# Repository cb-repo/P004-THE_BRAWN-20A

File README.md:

# THE BRAWN - 20A (v1.0)

THE BRAWN is a single DC-motor ESC: originally designed for insect-weight combat-robots, but is suitable for any appliction requiring a lightweight motor driver. 

Designed and built in [Christchurch, New Zealand ](https://www.google.co.nz/maps/place/Christchurch+New+Zealand) by Connor Benton, visit [cb-technology](https://www.cb-technology.co.nz/) for details.

## FEATURES
- Single Bi-Directional DC-motor output.
- Ultra-compact and lightweight.
- Under-voltage and reverse-polarity battery input protections.
- Run and status LED's.
- Instant power on and brown out recovery.
- Internal BEC for recievers.
- Includes a 100nF capacitor across the motor output to filter noise and voltage spikes.

## SPECIFICATIONS
- **Dimensions:** 20x15x4 mm
- **Weight:** 1.7g *excluding wires*
- **Input Voltage - Rated:** 1-3S lipo (3.3-12.6V)
- **Input Voltage - Absolute Max:** 18V
- **Output Current - Continuious:** 10A *(for more infomation see the Current Rating seciton)*
- **Output Current - Pulse:** 66A 
- **Motor Braking:** Enabled
- **BEC:** 3.3V, 200mA. Designed to power the radio reciever and other downstream ESC's but no motors or servos.
- **Signal Input:** Standard Servo PWM
     
## Fault Conditions
 - **Under-Voltage:** An under-voltage event occurs when the battery voltage falls below a pre-determined threshold.
    - At 3.6V (per cell) the device enters a warning state. This is only a warning and so functionality is not affected but the warning LED is illuminated for the operator.
    - At 3.4V (per cell) the device enters an under-voltage fault state. All motor functionality will be stopped until battery voltage is restored.
 - **Signal-Input:** A signal-input fault will occur if connection to the radio is lost for 50 ms. 
    - During a signal-input fault, a 'No Signal' fail-safe method is implemented and THE BRAWN will stop driving the motor output.
    - When a radio connection has been re-established the motor functionality is immediately resumed.

## LED Behaviour
There are two LEDs on THE BRAWN: 1x red Run LED and 1x green Status LED. The behaviour of each LED indicates what state the device is in.
 - **Normal Operation** Red: ON, Green: OFF
 - **Warning: Low Battery** Red: ON, Green: Flash
 - **Fault: Under-Voltage:** Red: Flash, Green: Flash
 - **Fault: Signal Input:** Red: OFF, Green: Flash

## Current Rating
The current rating of THE BRAWN is temperature-limited and so is very dependednt on the wires (gauge, length, and insulation) and avalible cooling. It is the responsibility of the user to choose the correct wires and test it appropriately before stressing the THE BRAWN in combat. 

As a guide, constant-current thermal testing has been conducted to illistrate the thermal characteristics. *Note: This test has been conducted at constant current, resulting in a higher temperature than the pulse currents in many drive applications.*

##### Reference testing parameters:
 - **Voltage:** 12V
 - **Motor Wire Length:** 100 mm
 - **Battery Wire Length:** 100 mm
 - **Wire Insulation:** PVC
 - **Ambient Temperature:** 23.5 °C
 - **PCB Heatshrink:** Yes
 - **ESC Cooling:** Open-Air passive cooling

##### Constant Current = 5A

##### Constant Current = 8A

##### Constant Current = 10A

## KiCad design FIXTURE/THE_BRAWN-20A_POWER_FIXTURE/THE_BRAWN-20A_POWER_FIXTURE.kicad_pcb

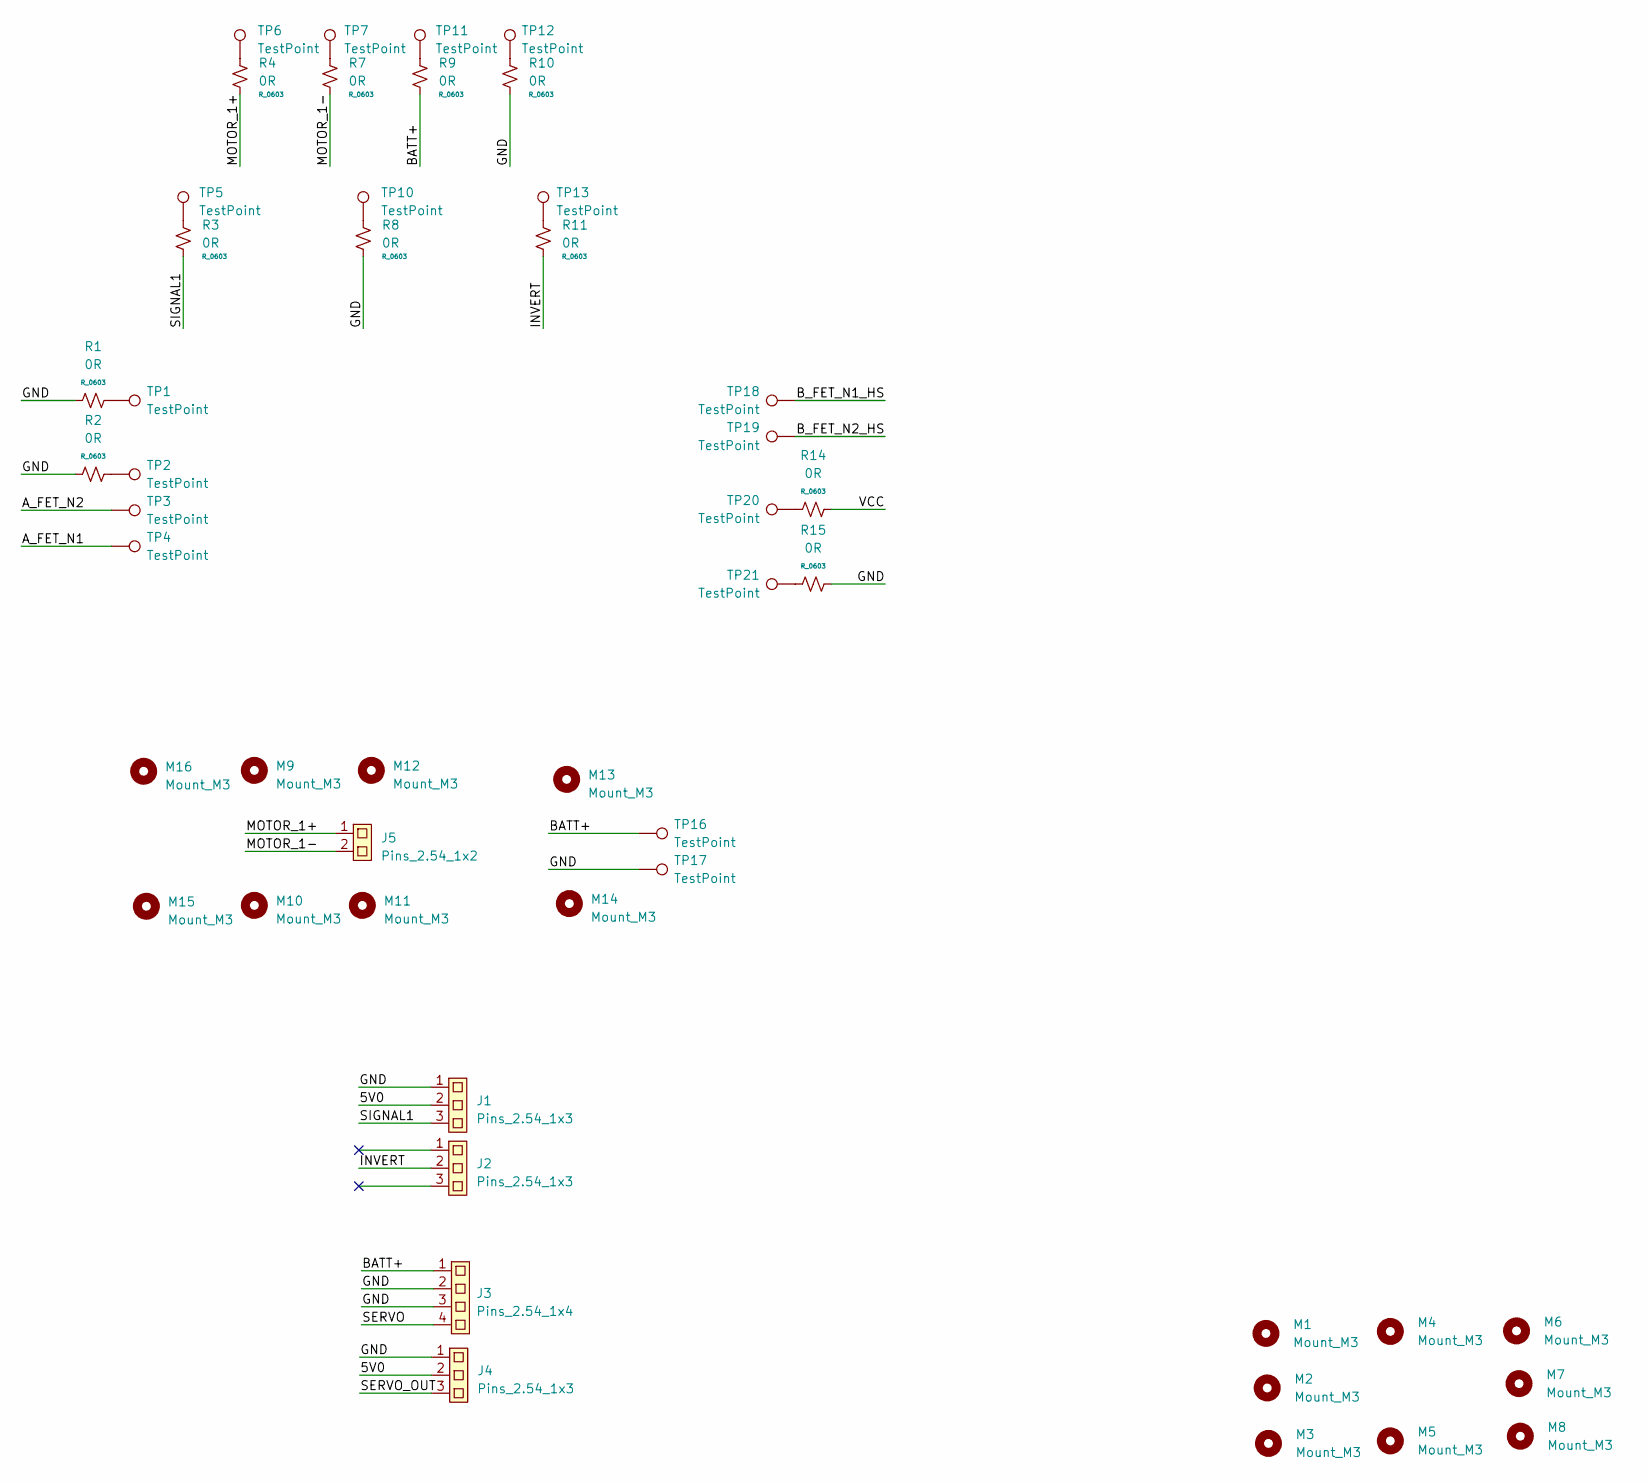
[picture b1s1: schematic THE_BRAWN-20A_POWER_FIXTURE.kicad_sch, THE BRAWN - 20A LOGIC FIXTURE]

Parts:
J1, J2, J4: Pins_2.54_1x3; Pins-2.54-1x3
J3: Pins_2.54_1x4; Pins-2.54-1x4
J5: Pins_2.54_1x2; Pins-2.54-1x2
M1, M2, M3, M4, M5, M6, M7, M8, M9, M10, M11, M12, M13, M14, M15, M16: Mount_M3
R1, R2, R3, R4, R7, R8, R9, R10, R11, R14, R15: 0R; R_0603
TP1, TP2, TP3, TP4, TP5, TP6, TP7, TP10, TP11, TP12, TP13, TP16, TP17, TP18, TP19, TP20, TP21: TestPoint; TestPoint_THTPad_D3.0mm_Drill1.5mm

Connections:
/5V0: J1.2, J4.2
/A_FET_N1: TP4.1
/A_FET_N2: TP3.1
/BATT+: J3.1, R9.2, TP16.1
/B_FET_N1_HS: TP18.1
/B_FET_N2_HS: TP19.1
/GND: J1.1, J3.2, J3.3, J4.1, R1.1, R2.1, R8.2, R10.2, R15.2, TP17.1
/INVERT: J2.2, R11.2
/MOTOR_1+: J5.1, R4.2
/MOTOR_1-: J5.2, R7.2
/SERVO: J3.4
/SERVO_OUT: J4.3
/SIGNAL1: J1.3, R3.2
/VCC: R14.2
unnamed: R1.2, TP1.1
unnamed: R2.2, TP2.1
unnamed: R3.1, TP5.1
unnamed: R4.1, TP6.1
unnamed: R7.1, TP7.1
unnamed: R8.1, TP10.1
unnamed: R9.1, TP11.1
unnamed: R10.1, TP12.1
unnamed: R11.1, TP13.1
unnamed: R14.1, TP20.1
unnamed: R15.1, TP21.1

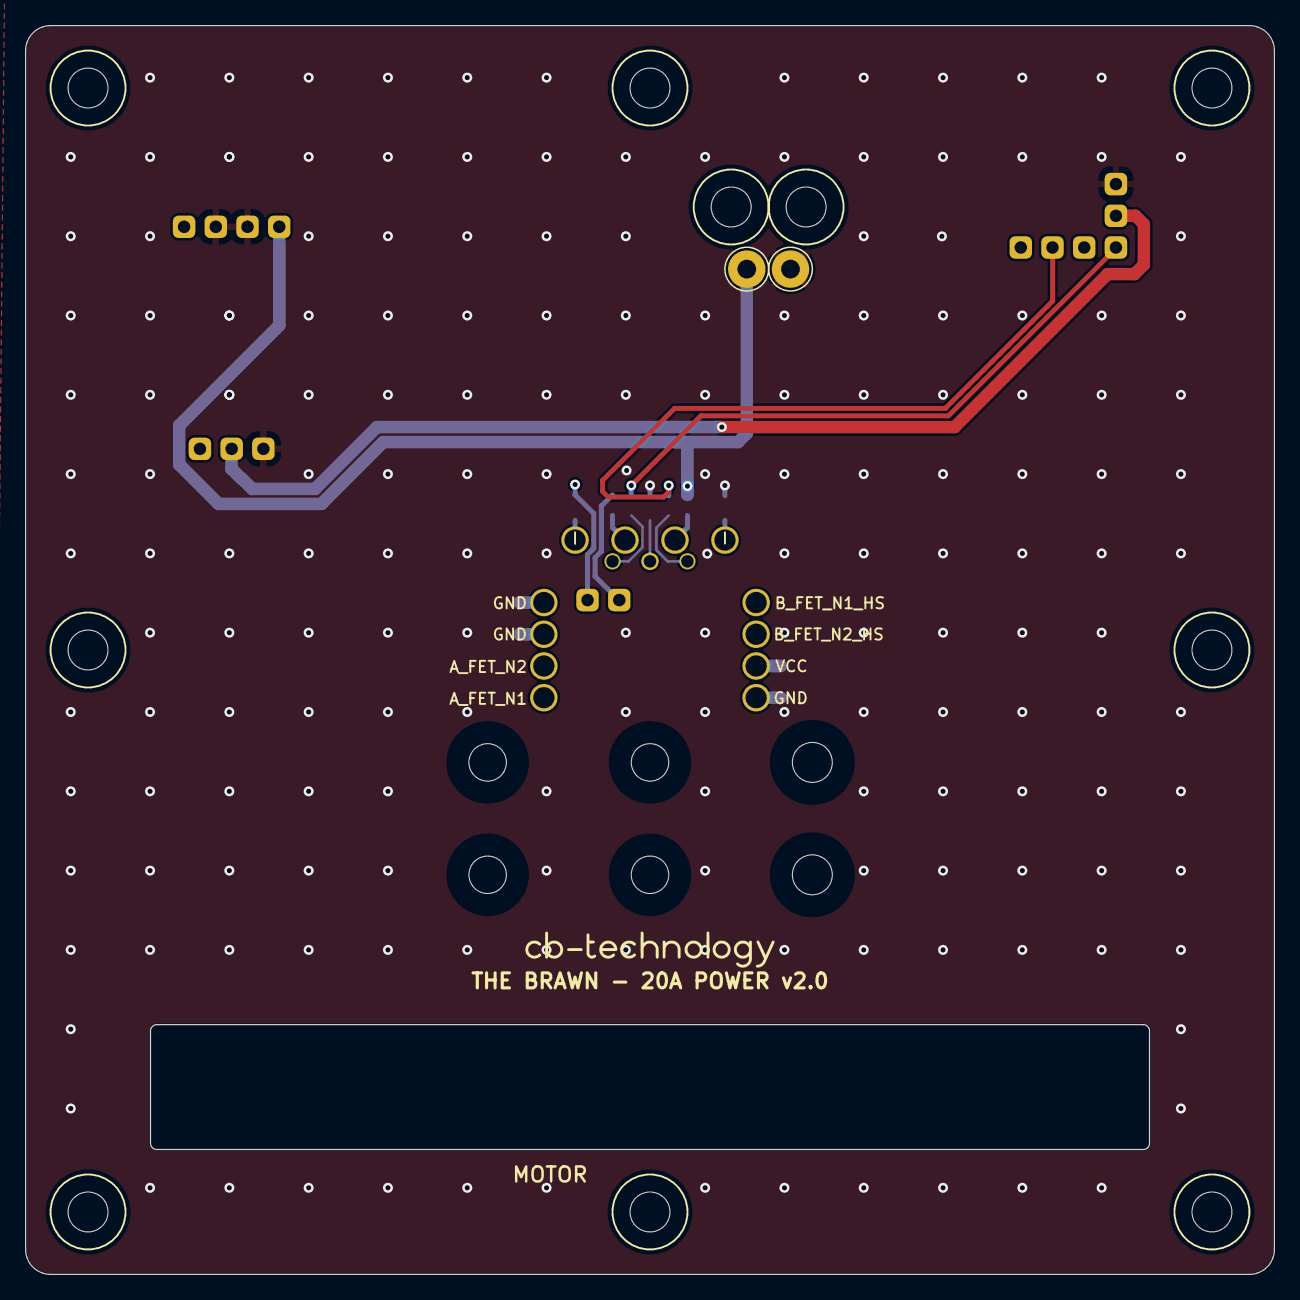
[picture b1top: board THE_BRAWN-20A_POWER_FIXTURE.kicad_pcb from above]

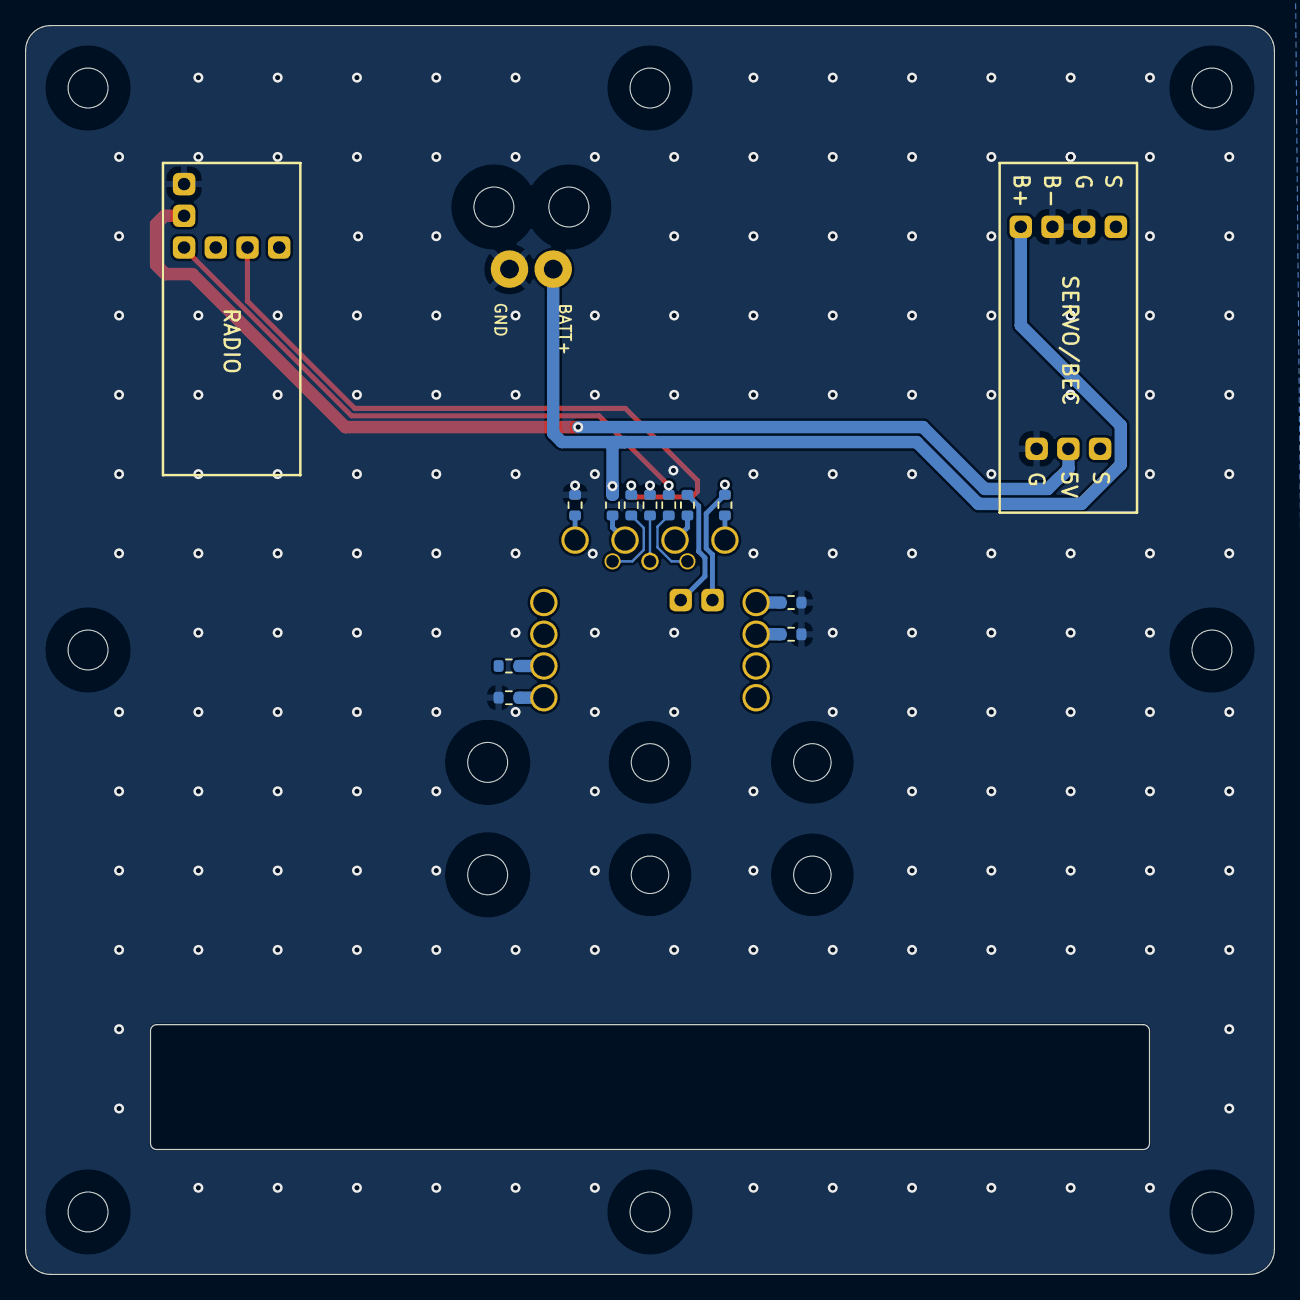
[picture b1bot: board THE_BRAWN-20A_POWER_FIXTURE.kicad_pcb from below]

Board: 2 copper layers, 100.0 x 100.0 mm, 49 parts (19 on the bottom side), 18 nets.

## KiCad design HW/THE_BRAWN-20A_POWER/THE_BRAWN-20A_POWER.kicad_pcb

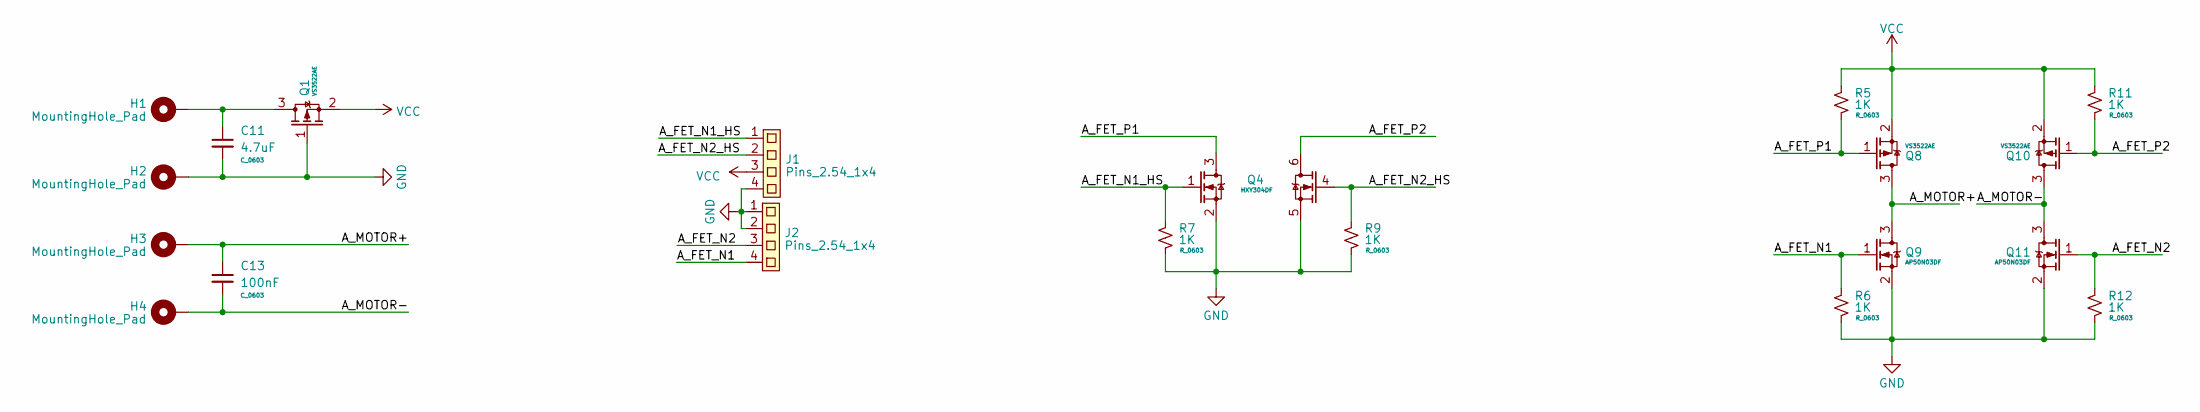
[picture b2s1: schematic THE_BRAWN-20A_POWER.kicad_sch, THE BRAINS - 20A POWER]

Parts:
C11: 4.7uF; C_0603
C13: 100nF; C_0603
H1, H2, H3, H4: MountingHole_Pad; MountingHole_2.2mm_M2_Pad_TopBottom
J1, J2: Pins_2.54_1x4; Pins-2.54-1x4
Q1, Q8, Q10: VS3522AE; 8-DFN_3x3
Q4: HXY304DF; 8-DFN_3x3_DUAL
Q9, Q11: AP50N03DF; 8-DFN_3x3
R5, R6, R7, R9, R11, R12: 1K; R_0603

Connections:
/A_FET_N1: J2.4, Q9.1 (G), R6.1
/A_FET_N1_HS: J1.1, Q4.1 (G), R7.1
/A_FET_N2: J2.3, Q11.1 (G), R12.1
/A_FET_N2_HS: J1.2, Q4.4 (G), R9.1
/A_FET_P1: Q4.3 (D), Q8.1 (G), R5.2
/A_FET_P2: Q4.6 (D), Q10.1 (G), R11.2
/A_MOTOR+: C13.1, H3.1, Q8.3 (D), Q9.3 (D)
/A_MOTOR-: C13.2, H4.1, Q10.3 (D), Q11.3 (D)
GND: C11.2, H2.1, J1.4, J2.1, J2.2, Q1.1 (G), Q4.2 (S), Q4.5 (S), Q9.2 (S), Q11.2 (S), R6.2, R7.2, R9.2, R12.2
unnamed: C11.1, H1.1, Q1.3 (D)
VCC: J1.3, Q1.2 (S), Q8.2 (S), Q10.2 (S), R5.1, R11.1

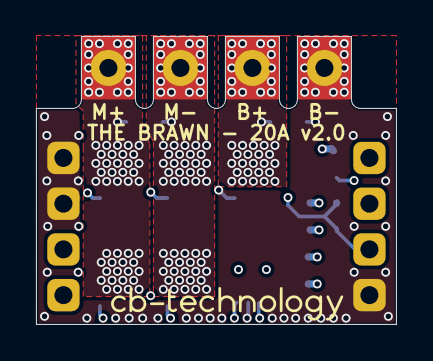
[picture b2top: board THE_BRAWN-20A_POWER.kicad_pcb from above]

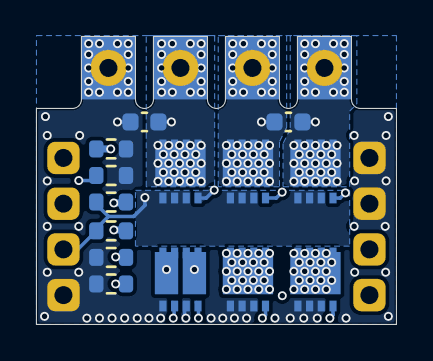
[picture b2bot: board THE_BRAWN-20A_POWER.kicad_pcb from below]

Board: 4 copper layers, 20.0 x 16.0 mm, 20 parts (14 on the bottom side), 11 nets.

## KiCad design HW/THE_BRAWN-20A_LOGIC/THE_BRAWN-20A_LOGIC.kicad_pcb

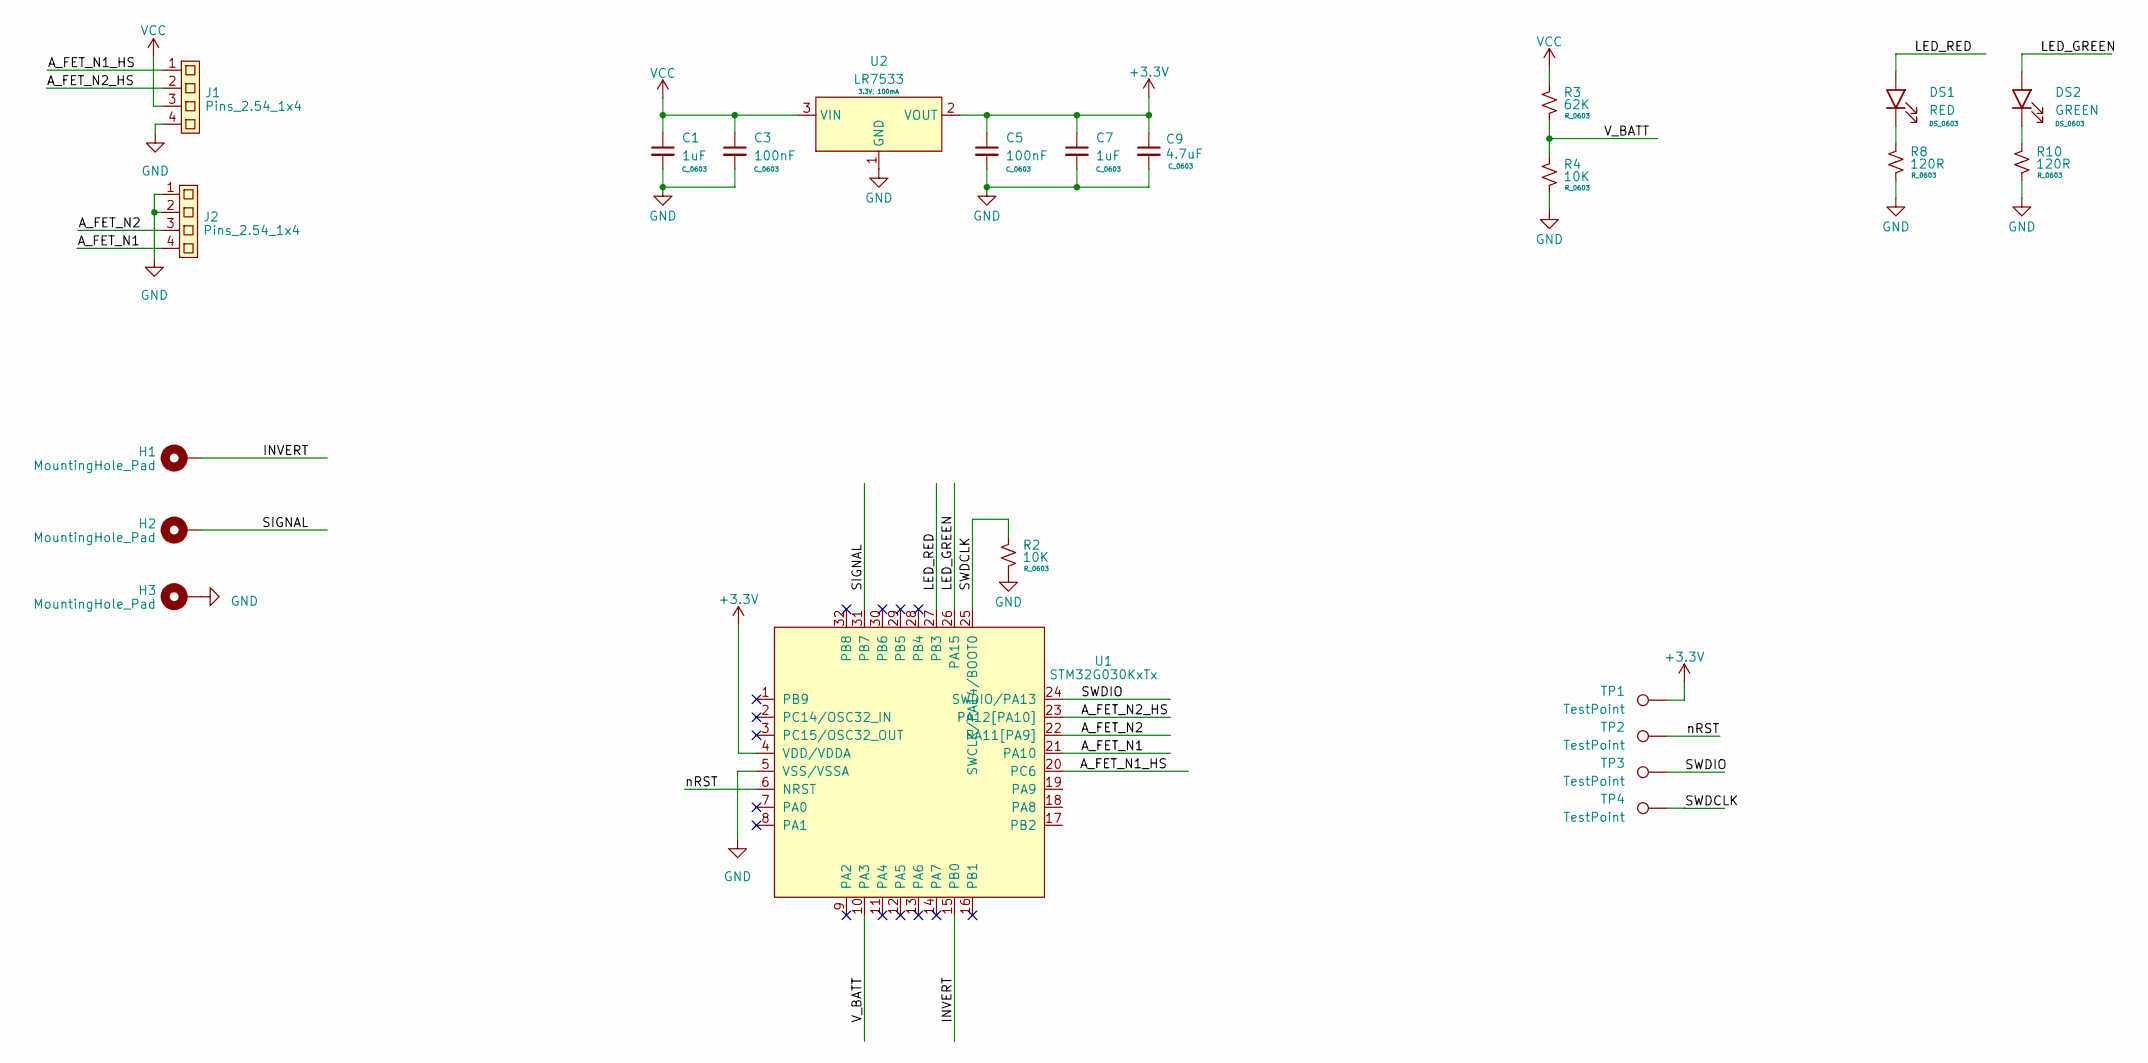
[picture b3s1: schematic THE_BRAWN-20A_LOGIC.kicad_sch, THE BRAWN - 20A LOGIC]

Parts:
C1, C7: 1uF; C_0603
C3, C5: 100nF; C_0603
C9: 4.7uF; C_0603
DS1: RED; DS_0603
DS2: GREEN; DS_0603
H1, H2, H3: MountingHole_Pad; MountingHole_2.2mm_M2_Pad_TopBottom
J1, J2: Pins_2.54_1x4; Pins-2.54-1x4
R2, R4: 10K; R_0603
R3: 62K; R_0603
R8, R10: 120R; R_0603
TP1, TP2, TP3, TP4: TestPoint; TestPoint_Pad_D1.5mm
U1: STM32G030KxTx; LQFP32_08_7x7
U2: LR7533; SOT23_3

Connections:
+3.3V: C5.1, C7.1, C9.1, TP1.1, U1.4 (VDD/VDDA), U2.2 (VOUT)
/A_FET_N1: J2.4, U1.21 (PA10)
/A_FET_N1_HS: J1.1, U1.20 (PC6)
/A_FET_N2: J2.3, U1.22 (PA11[PA9])
/A_FET_N2_HS: J1.2, U1.23 (PA12[PA10])
/INVERT: H1.1, U1.15 (PB0)
/LED_GREEN: DS2.2 (A), U1.26 (PA15)
/LED_RED: DS1.2 (A), U1.27 (PB3)
/SIGNAL: H2.1, U1.31 (PB7)
/SWDCLK: R2.1, TP4.1, U1.25 (SWCLK/PA14/BOOT0)
/SWDIO: TP3.1, U1.24 (SWDIO/PA13)
/V_BATT: R3.2, R4.1, U1.10 (PA3)
/nRST: TP2.1, U1.6 (NRST)
GND: C1.2, C3.2, C5.2, C7.2, C9.2, H3.1, J1.4, J2.1, J2.2, R2.2, R4.2, R8.2, R10.2, U1.5 (VSS/VSSA), U2.1 (GND)
unnamed: DS1.1 (K), R8.1
unnamed: DS2.1 (K), R10.1
VCC: C1.1, C3.1, J1.3, R3.1, U2.3 (VIN)

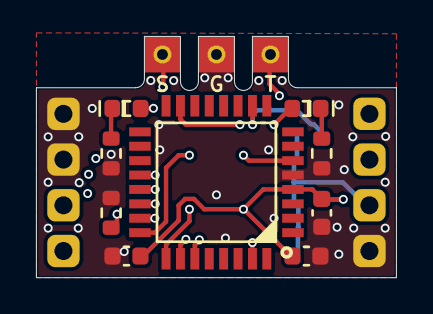
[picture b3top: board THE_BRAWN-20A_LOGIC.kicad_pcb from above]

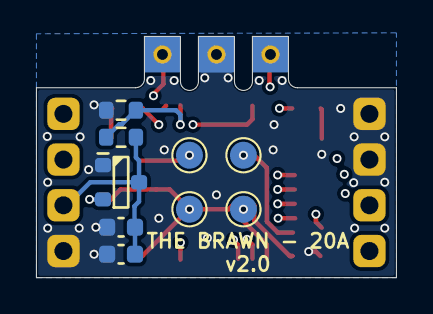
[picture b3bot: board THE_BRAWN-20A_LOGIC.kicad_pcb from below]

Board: 4 copper layers, 20.0 x 13.4 mm, 23 parts (9 on the bottom side), 17 nets.

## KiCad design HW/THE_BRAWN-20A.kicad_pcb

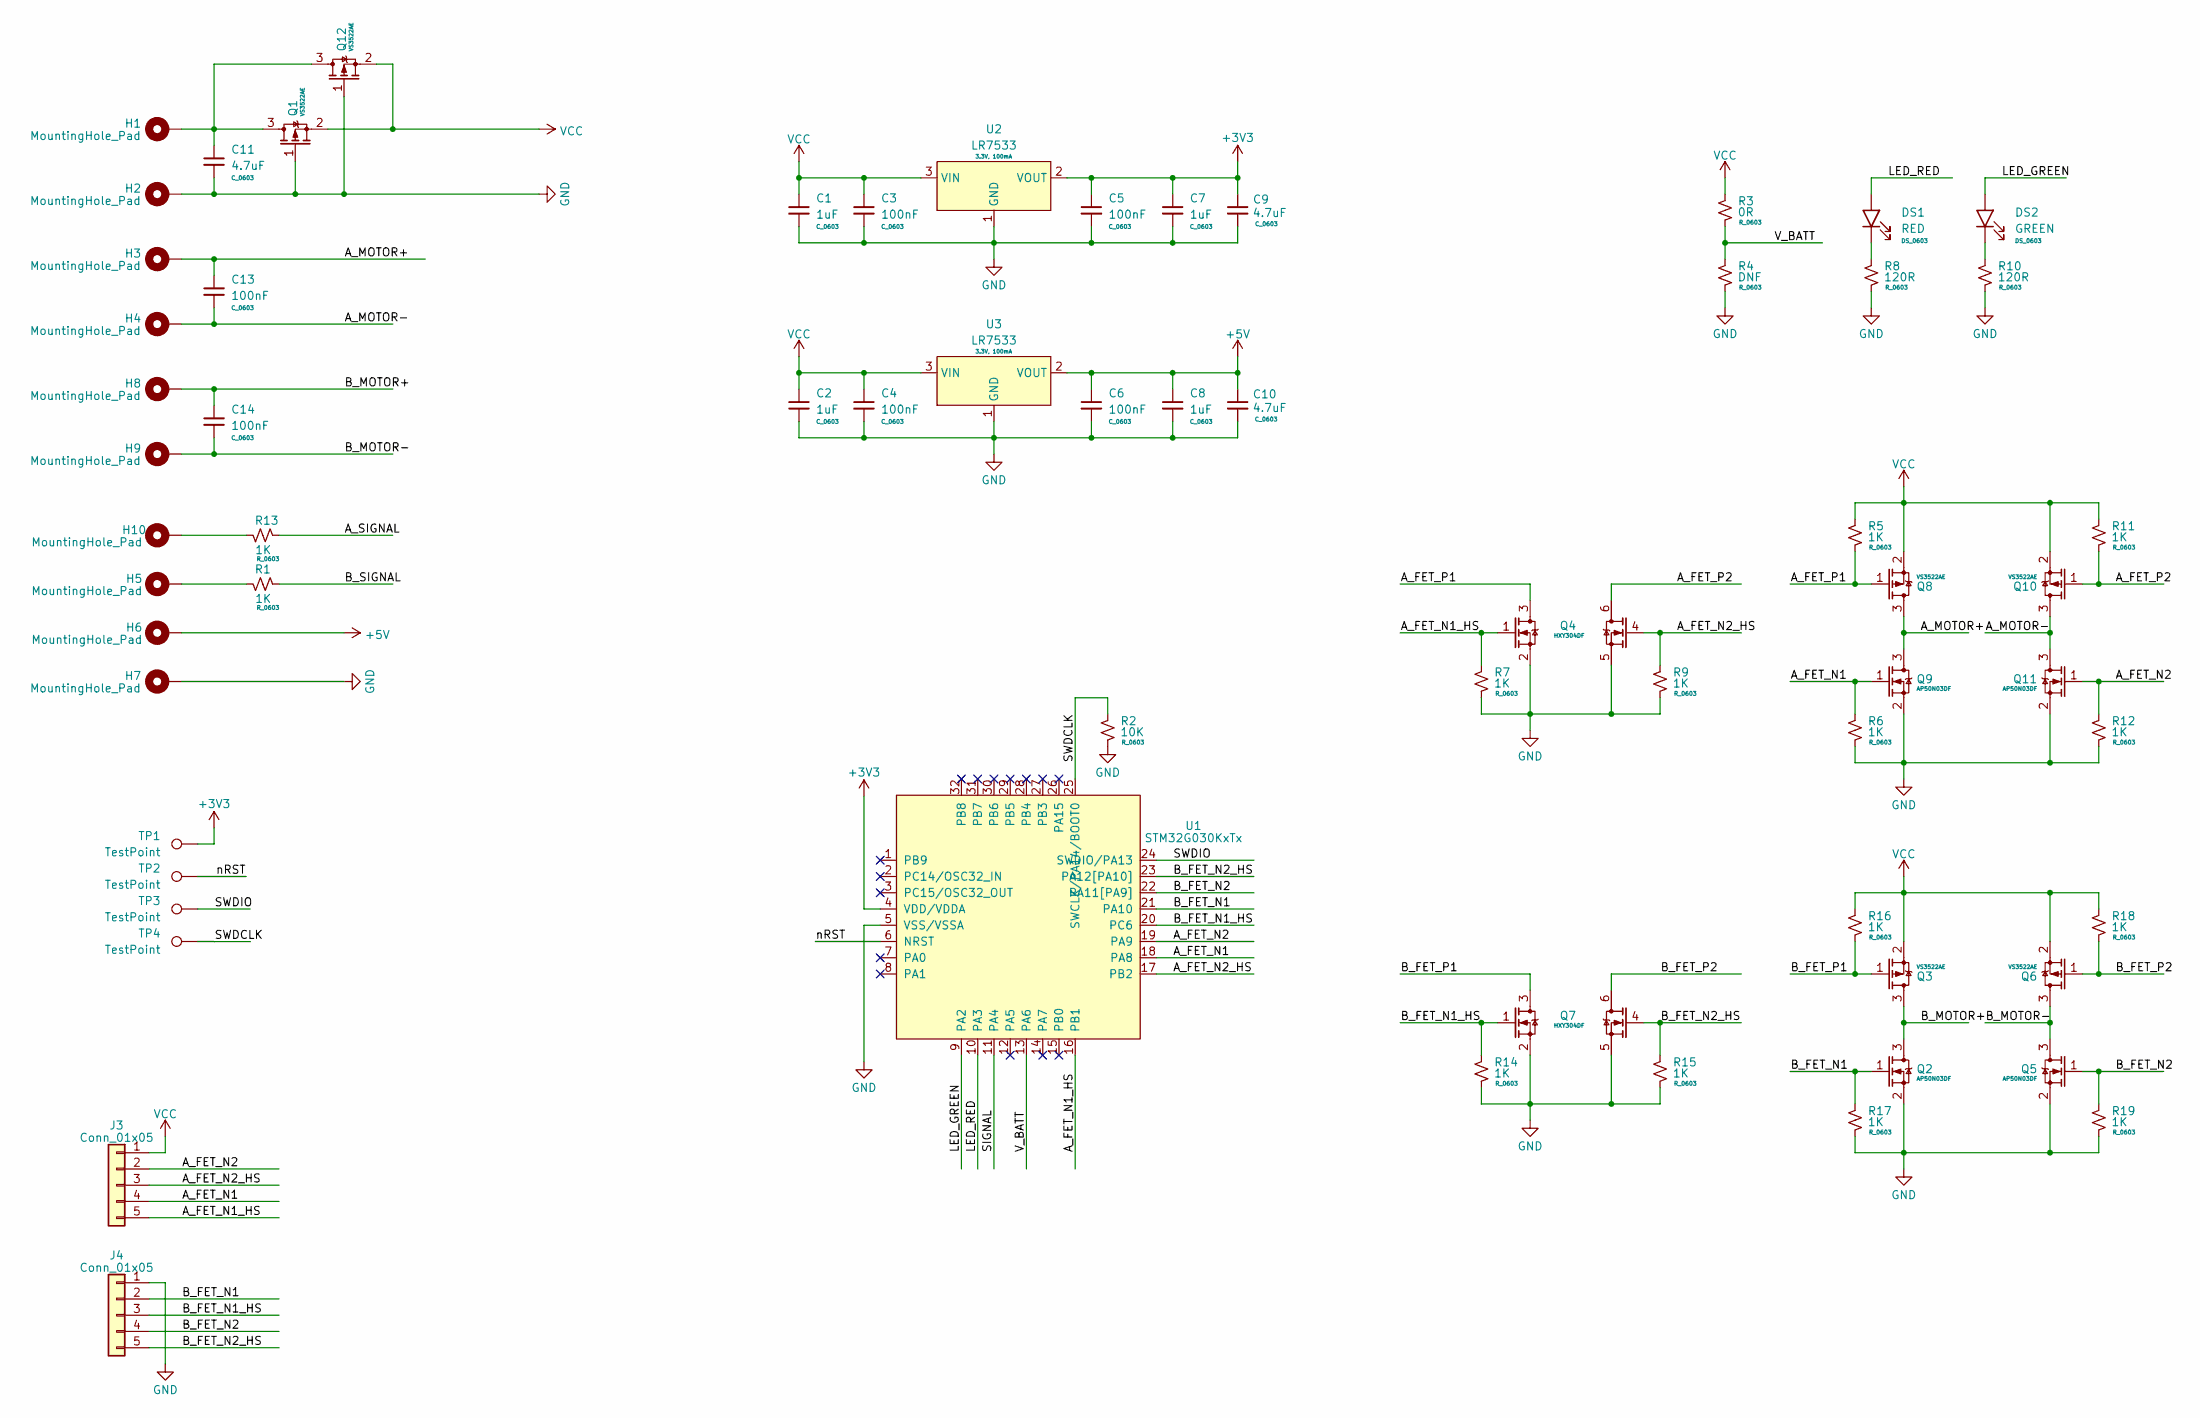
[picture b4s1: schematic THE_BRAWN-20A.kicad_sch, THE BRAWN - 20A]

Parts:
C1: 1uF; PinHeader_1x05_P2.54mm_Vertical
C2, C7, C8: 1uF; C_0603
C3, C4, C5, C6, C13, C14: 100nF; C_0603
C9, C10, C11: 4.7uF; C_0603
DS1: RED; DS_0603
DS2: GREEN; DS_0603
H1, H2, H3, H4, H5, H6, H7, H8, H9, H10: MountingHole_Pad; MountingHole_2.2mm_M2_Pad_TopBottom
J3, J4: Conn_01x05; PinHeader_1x05_P2.54mm_Vertical
Q1, Q3, Q6, Q8, Q10, Q12: VS3522AE; 8-DFN_3x3
Q2, Q5, Q9, Q11: AP50N03DF; 8-DFN_3x3
Q4, Q7: HXY304DF; 8-DFN_3x3_DUAL
R1, R5, R6, R7, R9, R11, R12, R13, R14, R15, R16, R17, R18, R19: 1K; R_0603
R2: 10K; R_0603
R3: 0R; R_0603
R4: DNF; R_0603
R8, R10: 120R; R_0603
TP1, TP2, TP3, TP4: TestPoint; TestPoint_Pad_D1.5mm
U1: STM32G030KxTx; LQFP32_08_7x7
U2, U3: LR7533; SOT23_3

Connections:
+3V3: C5.1, C7.1, C9.1, TP1.1, U1.4 (VDD/VDDA), U2.2 (VOUT)
+5V: C6.1, C8.1, C10.1, H6.1, U3.2 (VOUT)
/A_FET_N1: J3.4, Q9.1 (G), R6.1, U1.18 (PA8)
/A_FET_N1_HS: J3.5, Q4.1 (G), R7.1, U1.16 (PB1)
/A_FET_N2: J3.2, Q11.1 (G), R12.1, U1.19 (PA9)
/A_FET_N2_HS: J3.3, Q4.4 (G), R9.1, U1.17 (PB2)
/A_FET_P1: Q4.3 (D), Q8.1 (G), R5.2
/A_FET_P2: Q4.6 (D), Q10.1 (G), R11.2
/A_MOTOR+: C13.1, H3.1, Q8.3 (D), Q9.3 (D)
/A_MOTOR-: C13.2, H4.1, Q10.3 (D), Q11.3 (D)
/A_SIGNAL: R13.2
/B_FET_N1: J4.2, Q2.1 (G), R17.1, U1.21 (PA10)
/B_FET_N1_HS: J4.3, Q7.1 (G), R14.1, U1.20 (PC6)
/B_FET_N2: J4.4, Q5.1 (G), R19.1, U1.22 (PA11[PA9])
/B_FET_N2_HS: J4.5, Q7.4 (G), R15.1, U1.23 (PA12[PA10])
/B_FET_P1: Q3.1 (G), Q7.3 (D), R16.2
/B_FET_P2: Q6.1 (G), Q7.6 (D), R18.2
/B_MOTOR+: C14.1, H8.1, Q2.3 (D), Q3.3 (D)
/B_MOTOR-: C14.2, H9.1, Q5.3 (D), Q6.3 (D)
/B_SIGNAL: R1.2
/LED_GREEN: DS2.2 (A), U1.9 (PA2)
/LED_RED: DS1.2 (A), U1.10 (PA3)
/SIGNAL: U1.11 (PA4)
/SWDCLK: R2.1, TP4.1, U1.25 (SWCLK/PA14/BOOT0)
/SWDIO: TP3.1, U1.24 (SWDIO/PA13)
/V_BATT: R3.2, R4.1, U1.13 (PA6)
/nRST: TP2.1, U1.6 (NRST)
GND: C1.2, C2.2, C3.2, C4.2, C5.2, C6.2, C7.2, C8.2, C9.2, C10.2, C11.2, H2.1, H7.1, J4.1, Q1.1 (G), Q2.2 (S), Q4.2 (S), Q4.5 (S), Q5.2 (S), Q7.2 (S), Q7.5 (S), Q9.2 (S), Q11.2 (S), Q12.1 (G), R2.2, R4.2, R6.2, R7.2, R8.2, R9.2, R10.2, R12.2, R14.2, R15.2, R17.2, R19.2, U1.5 (VSS/VSSA), U2.1 (GND), U3.1 (GND)
unnamed: DS1.1 (K), R8.1
unnamed: DS2.1 (K), R10.1
unnamed: H5.1, R1.1
unnamed: H10.1, R13.1
unnamed: C11.1, H1.1, Q1.3 (D), Q12.3 (D)
VCC: C1.1, C2.1, C3.1, C4.1, J3.1, Q1.2 (S), Q3.2 (S), Q6.2 (S), Q8.2 (S), Q10.2 (S), Q12.2 (S), R3.1, R5.1, R11.1, R16.1, R18.1, U2.3 (VIN), U3.3 (VIN)

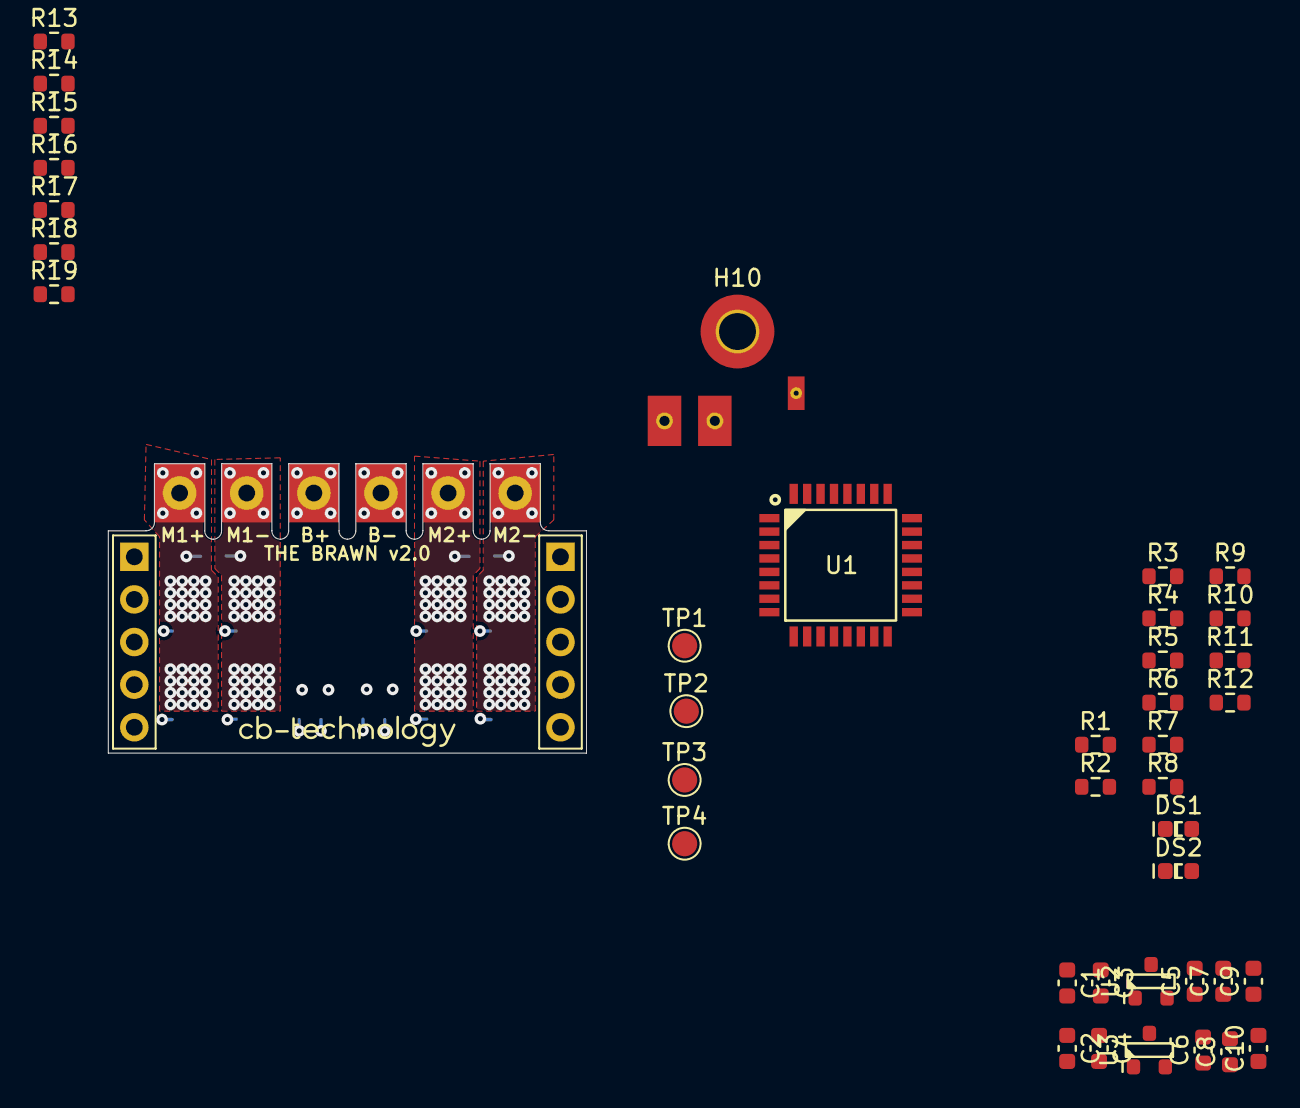
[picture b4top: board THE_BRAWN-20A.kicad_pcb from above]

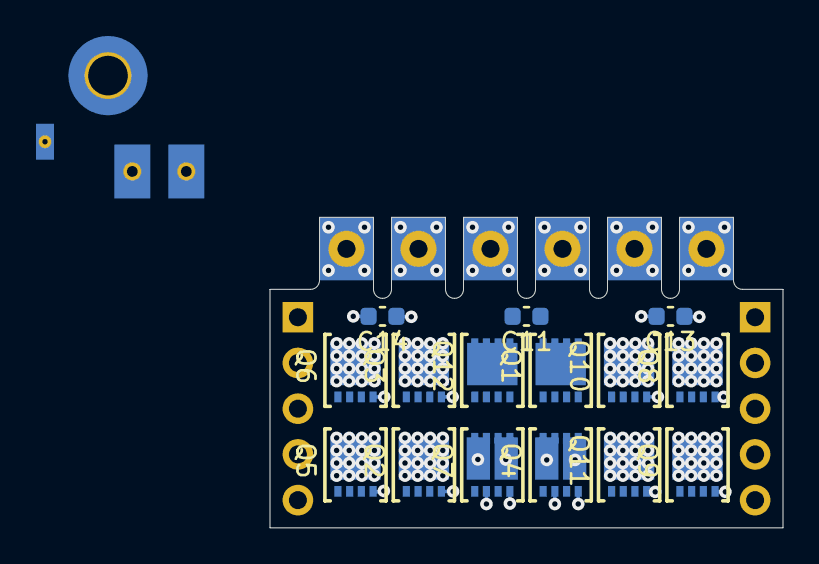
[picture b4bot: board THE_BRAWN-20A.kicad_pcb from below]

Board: 4 copper layers, 28.5 x 17.2 mm, 65 parts (15 on the bottom side), 31 nets.

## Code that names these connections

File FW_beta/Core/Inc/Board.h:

/* ~~~~~~~~~~~~~~~~~~~~~~~~~~~~~~~~~~~~~~~~~~~~~~~~~~ */
#ifndef BOARD_H
#define BOARD_H
/* ~~~~~~~~~~~~~~~~~~~~~~~~~~~~~~~~~~~~~~~~~~~~~~~~~~ */

#define STM32L0


#define CLK_PLL_MUL			4
#define CLK_PLL_DIV			2

// ADC CONFIG
#define ADC_VREF	      	3300

// TIM CONFIG
#define TIM_USE_IRQS
// 		Motor O/P
#define TIM2_ENABLE
#define TIM_MOTOR 			TIM_2
#define TIM_MOTOR_AF2		GPIO_AF2_TIM2
#define TIM_MOTOR_AF5		GPIO_AF5_TIM2
#define TIM_MOTOR_CH		0
#define TIM_MOTOR_RELOAD 	1000
#define TIM_MOTOR_FREQ		(MOTOR_FREQ*(TIM_MOTOR_RELOAD+1))
// 		Radio I/P
#define TIM21_ENABLE
#define TIM_RADIO 			TIM_21
#define TIM_RADIO_RELOAD 	0xffff
#define TIM_RADIO_FREQ		1000000


// UART CONFIG
// 		USART1_Tx - Pin30 (PA9)
//		USART1_Rx - Pin31	(PA10)
//#define RADIO_UART			USART2
//#define RADIO_GPIO			GPIOA
//#define RADIO_PINS			(GPIO_PIN_9 | GPIO_PIN_10)
//#define RADIO_AF		    GPIO_AF4_USART2
//#define UART_BFR_SIZE     	128


// IRQ CONFIG
#define GPIO_USE_IRQS
#define USE_EXTI_8
#define USE_EXTI_15
// 		Calibrate I/P - Pin18 (PA8)
#define CALIBRATE_GPIO		GPIOA
#define	CALIBRATE_PIN		GPIO_PIN_8
// 		Radio I/P - Pin25 (PA15) USART2_Rx
#define RADIO_GPIO			GPIOA
#define RADIO_PIN			GPIO_PIN_15


// DC-MOTOR H-BRIDGE CONFIG
/*
 * VSS --------------
 *  	|			|
 *     	P1			P2
 *     	|			|
 *     	|-- MOTOR --|
 *     	|			|
 *     	N1			N2
 *     	|	`		|
 * VCC --------------
 *
 * Note: P1 and P2 are P-FET, controlled through 2x Additional N-FET on the gate
 */
//		N1-FET O/P - Pin6 (PA0) TIM2_CH1
#define FET_N1_GPIO			GPIOA
#define FET_N1_PIN			GPIO_PIN_0
//		N2-FET O/P - Pin20 (PA10) TIM2 CH3
#define FET_N2_GPIO			GPIOA
#define FET_N2_PIN			GPIO_PIN_10
//		P1-FET O/P - Pin7 (PA1) TIM2_CH2
#define FET_P1_GPIO			GPIOA
#define FET_P1_PIN			GPIO_PIN_1
//		P2-FET O/P - Pin9 (PA3) TIM2 CH4
#define FET_P2_GPIO			GPIOA
#define FET_P2_PIN			GPIO_PIN_3

// IO CONFIG
// 		Battery Detect - Pin14 (PB0)
#define BATTERY_GPIO		GPIOB
#define	BATTERY_PIN			GPIO_PIN_0
#define BATTERY_CHANNEL		ADC_CHANNEL_8
#define BATTERY_DET_RLOW	1800
#define BATTERY_DET_RHIGH	10000
// 		Green LED - Pin3 (PC15)
#define LED_GRN_GPIO		GPIOC
#define LED_GRN_PIN			GPIO_PIN_15
// 		Red LED - Pin22 (PA12)
#define LED_RED_GPIO		GPIOA
#define LED_RED_PIN			GPIO_PIN_12


#endif /* BOARD_H */
/* ~~~~~~~~~~~~~~~~~~~~~~~~~~~~~~~~~~~~~~~~~~~~~~~~~~ */

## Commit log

2021-10-17 Initial WIP Commit
2021-10-23 Sync file structure
2022-01-01 Generate FW Project
2022-01-01 WIP Update STM32 Project
2022-01-10 Move WIP files to other PC
2022-01-22 Upload HW Files
2022-01-22 FW Dev for Beta Release
2022-01-22 CAD Design for Programming Clip
2022-01-23 Generate Readme Contents
2022-01-25 Update assets
2022-01-25 FW: Update fault/warning behaviour
2022-02-27 Synch latest WIP changes
2022-03-08 Code for Release rev0A
2022-03-20 Update Datasheet for Release
2022-03-21 Minor Updates to radio and and system faults
2022-07-23 Update Readme for release on CRNZ
2023-05-17 Add v1.0 DYMO label
2023-05-24 v2.0 WIP Commit
2023-05-26 Continue laying out PCB's
2023-05-29 Finish tracking Logic + Power PCB's for Manufacture
2023-05-29 Remove v1.0 Programmer Mechanical s
2023-05-29 Start Dev on Fixture PCB's
2023-05-30 Finish Tracking Logic Fixture PCB
2023-05-30 Finish Tracking Power Fixture PCB
2023-06-06 Update README Title
